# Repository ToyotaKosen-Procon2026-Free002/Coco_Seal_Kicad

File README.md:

# ココ・シール ハードウェア設計

## 表面実装部品

[JLCPCB表面実装可能部品検索](https://jlcpcb.com/parts)

データシートとか型番もここから持ってきたい

## データシートや製品ページ

### 基本的モジュール

- MCU(ESP32-C3-WROOM-02-N4)
  - [データシート](https://documentation.espressif.com/esp32-c3-wroom-02_datasheet_en.pdf)
  - [JLCPCB](https://jlcpcb.com/partdetail/3281215-ESP32_C3_WROOM_02N4/C2934560)
  - [購入ページ](https://akizukidenshi.com/catalog/g/g117493/)

- LoRa(E220-900T22S(JP))
  - [データシート](https://dragon-torch.tech/rf-modules/lora/e220-900t22s-jp/)
  - [購入ページ](https://akizukidenshi.com/catalog/g/g131361/)

- 3.3v 600mA レギュレータ(AP2112K-3.3TRG1)
  - [JLCPCB](https://jlcpcb.com/partdetail/TECHPUBLIC-AP2112K_33TRG1/C23380830)
  - [データシート](./datasheets/AP2112K.pdf)

- OLED(SSD1306)
  - [データシート](https://akizukidenshi.com/goodsaffix/ssd1306.pdf)
  - [購入ページ](https://akizukidenshi.com/catalog/g/g112031/)

- ブザー(PKB24SPCH3601-B0)
  - [JLCPCB](https://jlcpcb.com/partdetail/MurataElectronics-PKB24SPCH3601B0/C440255)
  - [データシート](https://akizukidenshi.com/goodsaffix/murata-piezo-buzzer.pdf)

- 2色LED(LT6CU7R)
  - [購入ページ](https://akizukidenshi.com/catalog/g/g108982/)
  - [データシート](https://akizukidenshi.com/goodsaffix/LT6CU7R.pdf)

### バッテリー回路

- 充電IC(TP4056-42-ESOP8)
  - [JLCPCB](https://jlcpcb.com/partdetail/17264-TP4056_42ESOP8/C16581)
  - [データシート](https://www.lcsc.com/datasheet/C16581.pdf)

- Li-ion保護IC(DW01A)
  - [JLCPCB](https://jlcpcb.com/partdetail/PUOLOP-DW01A/C351410)
  - [データシート](https://hmsemi.com/downfile/DW01A.PDF)

- デュアルMOSFET(FS8205A)
  - [JLCPCB](https://jlcpcb.com/partdetail/TECHPUBLIC-FS8205A/C2830320)
  - [データシート](./datasheets/FS8205A.pdf)

### 基本部品

- コンデンサ
  - 0.1μF [JLCPCB](https://jlcpcb.com/partdetail/YAGEO-CC0603KRX7R9BB104/C14663)
  - 1μF [JLCPCB](https://jlcpcb.com/partdetail/16531-CL10A105KB8NNNC/C15849)
  - 10μF [JLCPCB](https://jlcpcb.com/partdetail/14236-CL31A106KBHNNNE/C13585)
  - 470μF [JLCPCB](https://jlcpcb.com/partdetail/HonorElec-RVT1C471M0810/C3341)

- USB-Cコネクタ
  - [JLCPCB](https://jlcpcb.com/partdetail/SHOUHAN-TYPE_C_16PIN_2MD_073/C2765186)

- 抵抗
  - 100 [JLCPCB](https://jlcpcb.com/partdetail/23502-0603WAF1000T5E/C22775)
  - 330 [JLCPCB](https://jlcpcb.com/partdetail/23865-0603WAF3300T5E/C23138)
  - 1k [JLCPCB](https://jlcpcb.com/partdetail/21904-0603WAF1001T5E/C21190)
  - 10k [JLCPCB](https://jlcpcb.com/partdetail/26547-0603WAF1002T5E/C25804)
  - 4.7k [JCLPCB](https://jlcpcb.com/partdetail/23889-0603WAF4701T5E/C23162)
  - 5.1k [JLCPCB](https://jlcpcb.com/partdetail/23913-0603WAF5101T5E/C23186)
  - 100k [JLCPCB](https://jlcpcb.com/partdetail/26546-0603WAF1003T5E/C25803)

- タクトスイッチ
  - SOS [購入ページ](https://akizukidenshi.com/catalog/g/g109827/)
  - Common [JLCPCB](https://jlcpcb.com/partdetail/SHOUHAN-TS665TPZJ/C557600)
  - Reset [JLCPCB](https://jlcpcb.com/partdetail/Korean_HropartsElec-K2_6639DP_B4SW04/C83205)

### その他

- ESD保護素子(D+D-の静電気などの保護)(TPD2EUSB30A)
  - [JLCPCB](https://jlcpcb.com/partdetail/TexasInstruments-TPD2EUSB30ADRTR/C94934)
  - [データシート](https://www.ti.com/cn/lit/ds/symlink/tpd2eusb30a.pdf)

- MMOSFET(AO3400A)
  - [JLCPCB](https://jlcpcb.com/partdetail/Alpha_OmegaSemicon-AO3400A/C20917)
  - [データシート](./datasheets/AO3400A.pdf)

## GPIO割り当て

Strapping pins に割り当てられているため、2, 8, 9 はちょっと使いづらい

|GPIO|機能|入出力|周辺回路|プルアップ/プルダウン|備考|
|:-:|:-:|:-:|:-:|:-:|:-:|
|0|ADC|IN|バッテリー電圧分圧回路|-|R1=R2=100kΩくらい|
|1|GPIO|IN|タクトスイッチ1|プルアップ|
|2|GPIO|OUT|2色LED_R|プルアップ|Strapping Pin, 起動時に誤点灯の可能性あり|
|3|GPIO|OUT|ブザー制御MOSFET|-|MOSFETを通してバッテリーから直で電源供給予定|
|4|I2C|I/O|OLED SCK|-|おそらくモジュール側でPU実装済|
|5|I2C|I/O|OLED SDA|-|おそらくモジュール側でPU実装済|
|6|GPIO|OUT|LoRa M1|-|
|7|GPIO|OUT|LoRa M0|-|
|8|GPIO|OUT|2色LED_G|プルアップ|Strapping Pin, 起動時に誤点灯の可能性あり|
|9|GPIO|IN|タクトスイッチ2|プルアップ|Strapping Pin, 押しながら起動するとDownload Mode として起動|
|10|GPIO|IN|LoRa AUX|-|
|18|USB D-|I/O|USB-C D-|-|ESD保護素子を挟む|
|19|USB D+|I/O|USB-C D+|-|ESD保護素子を挟む|
|20|UART TXD|OUT|LoRa RXD|-|固定|
|21|UART RXD|IN|LoRa TXD|-|固定|

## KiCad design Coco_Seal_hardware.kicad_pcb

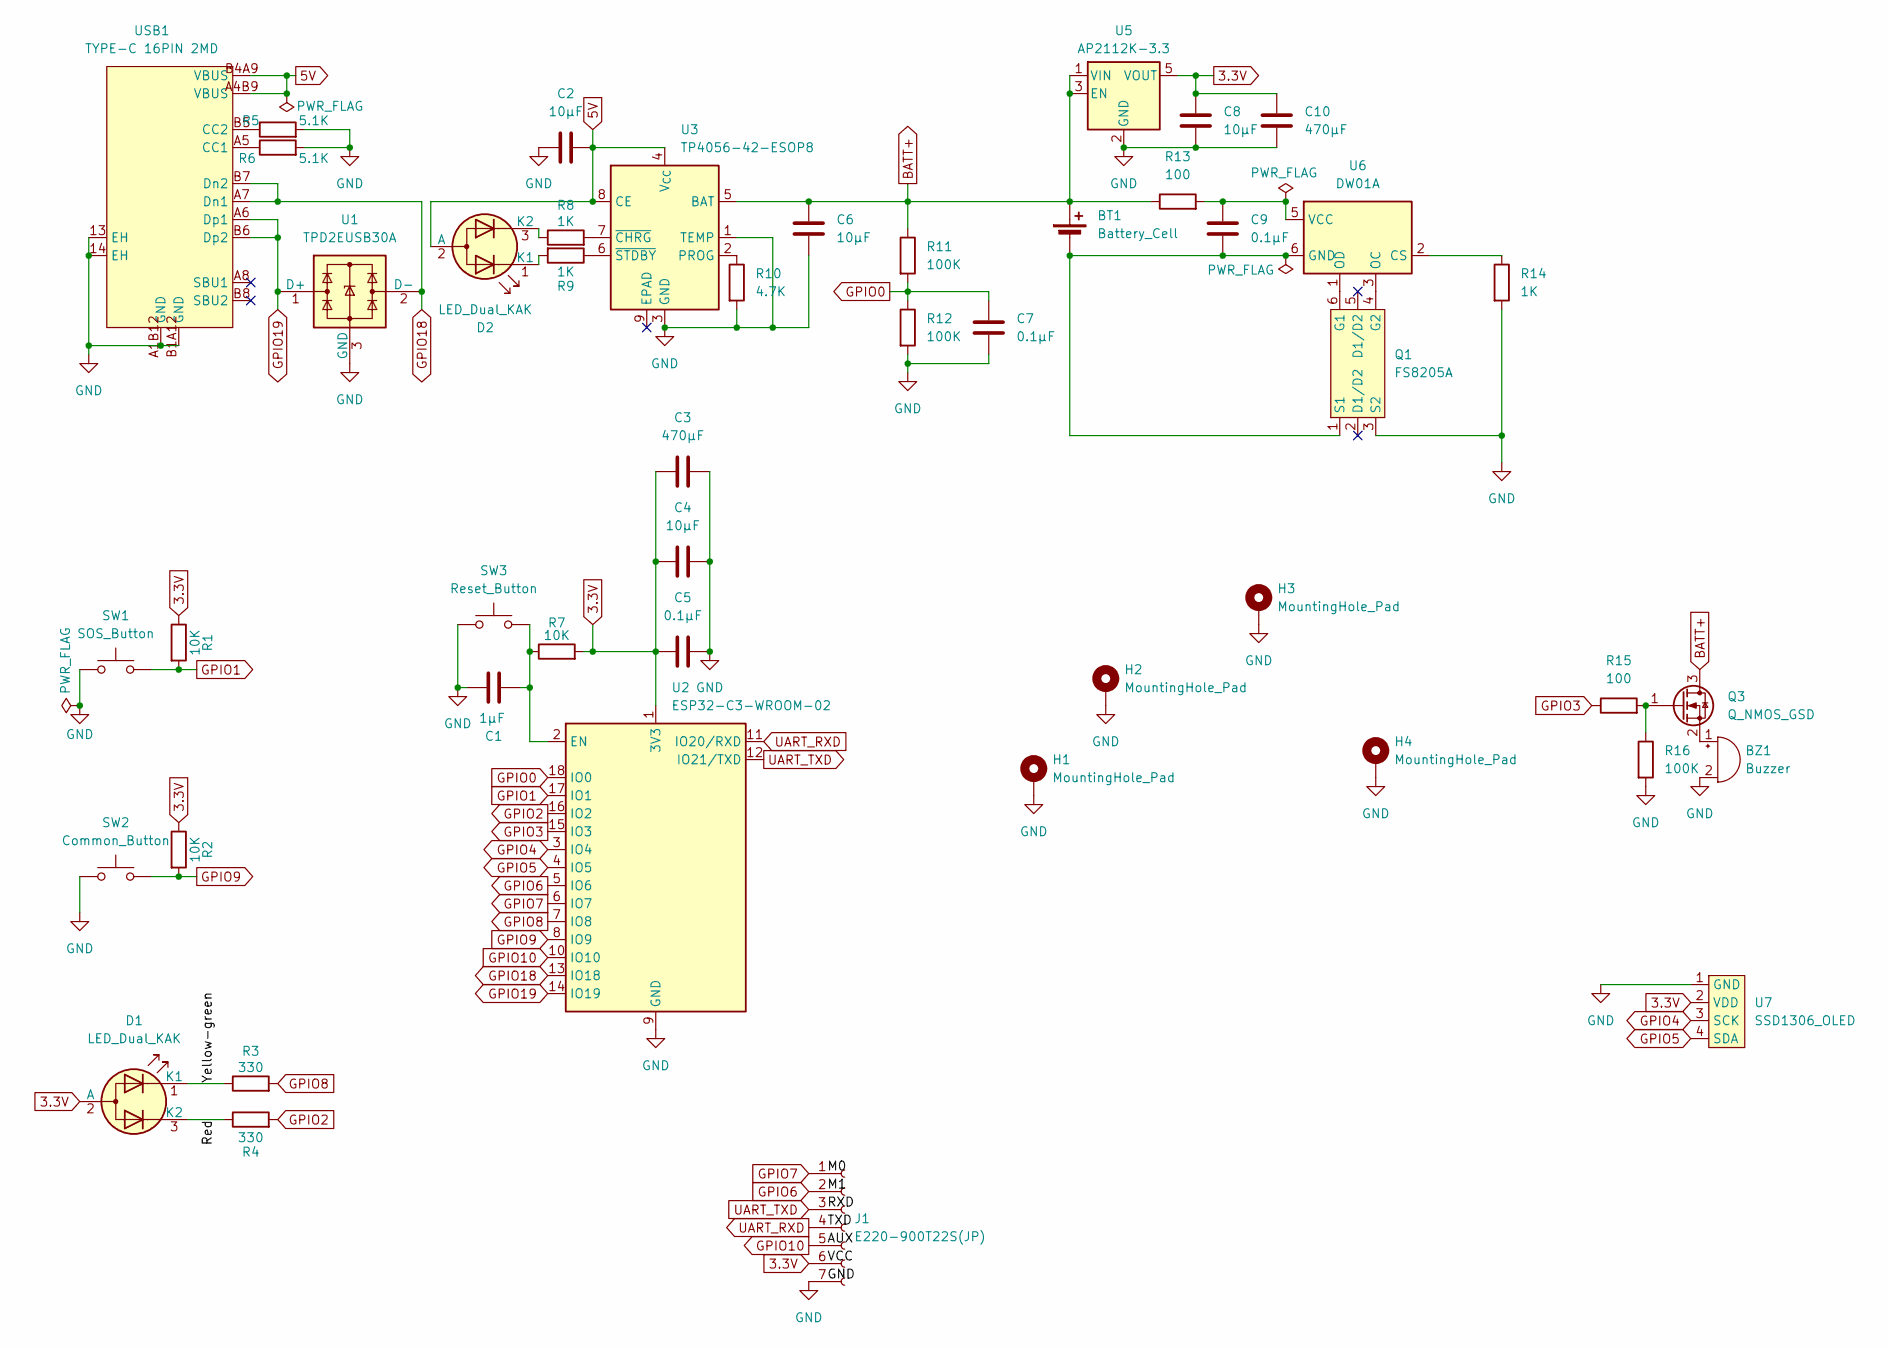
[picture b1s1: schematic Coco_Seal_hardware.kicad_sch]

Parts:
BT1: Battery_Cell; JST_PH_S2B-PH-K_1x02_P2.00mm_Horizontal
BZ1: Buzzer; BUZ-TH_BD24.3-P15.00_PKB24SPCH3601-B0
C1: 1μF; C0603; LCSC Part C15849
C2, C4, C6, C8: 10μF; C1206; LCSC Part C13585
C3, C10: 470μF; CAP-SMD_BD8.0-L8.3-W8.3-FD; LCSC Part C3341
C5, C7, C9: 0.1μF; C0603; LCSC Part C14663
D1, D2: LED_Dual_KAK; LED_D5.0mm-3
H1, H2, H3, H4: MountingHole_Pad; MountingHole_3.2mm_M3_ISO7380_Pad_TopBottom
J1: E220-900T22S(JP); PinSocket_1x07_P2.54mm_Vertical
Q1: FS8205A; SOT-23-6; LCSC Part C2830320
Q3: Q_NMOS_GSD; SOT-23-3; LCSC Part C20917
R1, R2, R7: 10K; R0603; LCSC Part C25804
R3, R4: 330; R0603; LCSC Part C23138
R5, R6: 5.1K; R0603; LCSC Part C23186
R8, R9, R14: 1K; R0603; LCSC Part C21190
R10: 4.7K; R0603; LCSC Part C23162
R11, R12, R16: 100K; R0603; LCSC Part C25803
R13, R15: 100; R0603; LCSC Part C22775
SW1: SOS_Button; SW_PUSH-12mm
SW2: Common_Button; SW-TH_TS665TPZJ; LCSC Part C557600
SW3: Reset_Button; SW_PUSH_6mm; LCSC Part C97440
U1: TPD2EUSB30A; Texas_DRT-3; LCSC Part C94934
U2: ESP32-C3-WROOM-02; LCSC Part C2934560
U3: TP4056-42-ESOP8; SOIC-8-1EP_3.9x4.9mm_P1.27mm_EP2.41x3.3mm_ThermalVias; LCSC Part C16581
U5: AP2112K-3.3; SOT-23-5; LCSC Part C23380830
U6: DW01A; SOT-23-6; LCSC Part C351410
U7: SSD1306_OLED; PinSocket_1x04_P2.54mm_Vertical
USB1: TYPE-C 16PIN 2MD; USB-C-SMD_TYPE-C-16PIN-2MD-073; MPN TYPE-C 16PIN 2MD(073); LCSC Part C2765186

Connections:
3.3V: C3.1, C4.1, C5.1, C8.1, C10.1, D1.2 (A), J1.6, R1.1, R2.1, R7.2, U2.1 (3V3), U5.5 (VOUT), U7.2 (VDD)
5V: C2.1, D2.2 (A), U3.4 (V_{CC}), U3.8 (CE), USB1.A4B9 (VBUS), USB1.B4A9 (VBUS)
/Red: D1.3 (K2), R4.1
/Yellow-green: D1.1 (K1), R3.1
BATT+: BT1.1 (+), C6.1, Q3.3 (D), R11.1, R13.1, U3.5 (BAT), U5.1 (VIN), U5.3 (EN)
GND: BZ1.2 (-), C1.2, C2.2, C3.2, C4.2, C5.2, C6.2, C7.2, C8.2, C10.2, H1.1 (1_1), H2.1 (1_1), H3.1 (1_1), H4.1 (1_1), J1.7, Q1.3 (S2), R5.2, R6.2, R10.2, R12.2, R14.2, R16.2, SW1.1, SW2.1, SW3.1, U1.3 (GND), U2.9 (GND), U2.19 (GND), U3.1 (TEMP), U3.3 (GND), U5.2 (GND), U7.1 (GND), USB1.13 (EH), USB1.14 (EH), USB1.A1B12 (GND), USB1.B1A12 (GND)
GPIO0: C7.1, R11.2, R12.1, U2.18 (IO0)
GPIO1: R1.2, SW1.2, U2.17 (IO1)
GPIO2: R4.2, U2.16 (IO2)
GPIO3: R15.1, U2.15 (IO3)
GPIO4: U2.3 (IO4), U7.3 (SCK)
GPIO5: U2.4 (IO5), U7.4 (SDA)
GPIO6: J1.2, U2.5 (IO6)
GPIO7: J1.1, U2.6 (IO7)
GPIO8: R3.2, U2.7 (IO8)
GPIO9: R2.2, SW2.2, U2.8 (IO9)
GPIO10: J1.5, U2.10 (IO10)
GPIO18: U1.2 (D-), U2.13 (IO18), USB1.A7 (Dn1), USB1.B7 (Dn2)
GPIO19: U1.1 (D+), U2.14 (IO19), USB1.A6 (Dp1), USB1.B6 (Dp2)
unnamed: BT1.2 (-), C9.2, Q1.1 (S1), U6.6 (GND)
unnamed: BZ1.1 (+), Q3.2 (S)
unnamed: D2.1 (K1), R9.2
unnamed: D2.3 (K2), R8.1
unnamed: Q1.6 (G1), U6.1 (OD)
unnamed: Q1.4 (G2), U6.3 (OC)
unnamed: Q3.1 (G), R15.2, R16.1
unnamed: C1.1, R7.1, SW3.2, U2.2 (EN)
unnamed: R10.1, U3.2 (PROG)
unnamed: R8.2, U3.7 (~CHRG)
unnamed: R9.1, U3.6 (~STDBY)
unnamed: R14.1, U6.2 (CS)
unnamed: C9.1, R13.2, U6.5 (VCC)
unnamed: R6.1, USB1.A5 (CC1)
unnamed: R5.1, USB1.B5 (CC2)
UART_RXD: J1.4, U2.11 (IO20/RXD)
UART_TXD: J1.3, U2.12 (IO21/TXD)

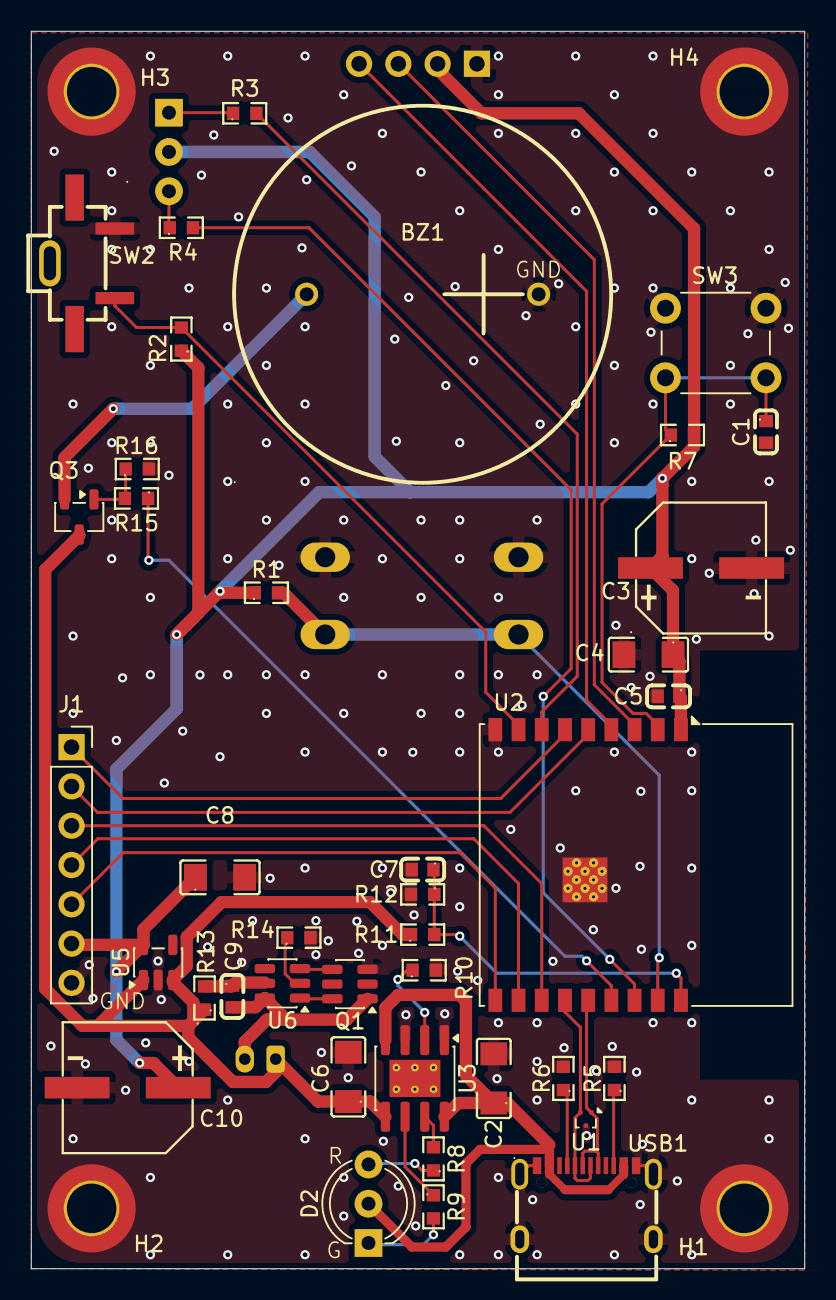
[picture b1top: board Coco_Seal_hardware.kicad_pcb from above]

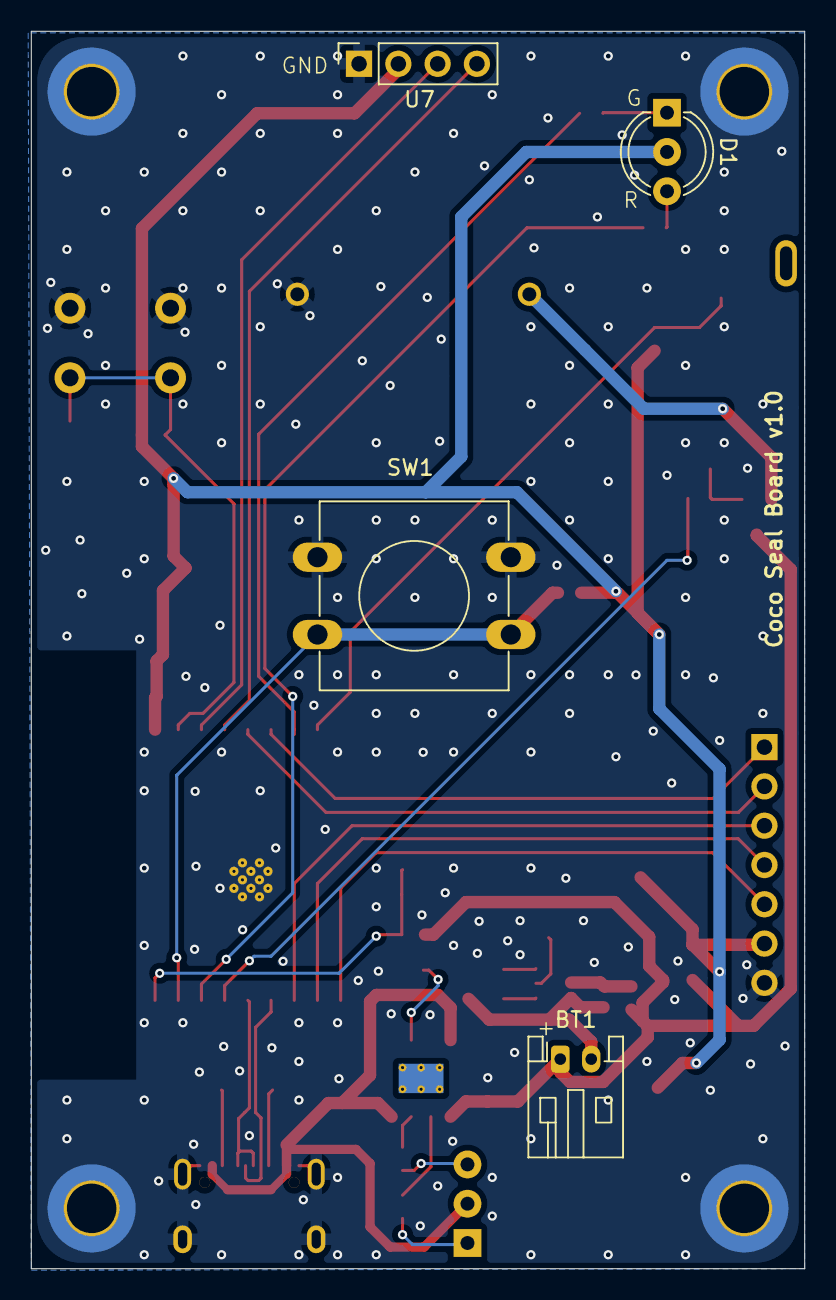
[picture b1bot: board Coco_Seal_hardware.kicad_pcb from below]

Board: 2 copper layers, 50.0 x 80.0 mm, 47 parts (4 on the bottom side), 36 nets.

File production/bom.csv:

Designator,Footprint,Quantity,Value,LCSC Part #
BT1,JST_PH_S2B-PH-K_1x02_P2.00mm_Horizontal,1,Battery_Cell,
BZ1,BUZ-TH_BD24.3-P15.00_PKB24SPCH3601-B0,1,Buzzer,C440255
C1,C0603,1,1μF,C15849
"C10, C3",CAP-SMD_BD8.0-L8.3-W8.3-FD,2,470μF,C3341
"C2, C4, C6, C8",C1206,4,10μF,C13585
"C5, C7, C9",C0603,3,0.1μF,C14663
"D1, D2",LED_D5.0mm-3,2,LED_Dual_KAK,
J1,PinSocket_1x07_P2.54mm_Vertical,1,E220-900T22S(JP),
Q1,SOT-23-6,1,FS8205A,C2830320
Q3,SOT-23-3,1,Q_NMOS_GSD,C20917
"R1, R2, R7",R0603,3,10K,C25804
R10,R0603,1,4.7K,C23162
"R11, R12, R16",R0603,3,100K,C25803
"R13, R15",R0603,2,100,C22775
"R14, R8, R9",R0603,3,1K,C21190
"R3, R4",R0603,2,330,C23138
"R5, R6",R0603,2,5.1K,C23186
SW1,SW_PUSH-12mm,1,SOS_Button,
SW2,SW-TH_TS665TPZJ,1,Common_Button,C557600
SW3,SW_PUSH_6mm,1,Reset_Button,C97440
U1,Texas_DRT-3,1,TPD2EUSB30A,C94934
U2,ESP32-C3-WROOM-02,1,ESP32-C3-WROOM-02,C2934560
U3,SOIC-8-1EP_3.9x4.9mm_P1.27mm_EP2.41x3.3mm_ThermalVias,1,TP4056-42-ESOP8,C16581
U5,SOT-23-5,1,AP2112K-3.3,C23380830
U6,SOT-23-6,1,DW01A,C351410
U7,PinSocket_1x04_P2.54mm_Vertical,1,SSD1306_OLED,
USB1,USB-C-SMD_TYPE-C-16PIN-2MD-073,1,TYPE-C 16PIN 2MD,C2765186
